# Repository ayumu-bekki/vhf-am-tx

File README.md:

# vhf-am-tx

Seeed Studio XIAO ESP32C6 を用いた 144MHz帯 終段ドレイン変調 AM(A1A / A2A / A3E)送信機プロジェクト。
ARDF(アマチュア無線方向探知)用のフォックスハンティング送信機(A2A)、手動キーのCW送信機(A1A)、および音声AM送信機(A3E)として動作します。

## 主な仕様

- **送信周波数**: 144.000 〜 146.000 MHz(20 kHz ステップ、Si5351A PLL制御)
- **電波型式**:
  - **A1A**: 搬送波断続の電信(CWモード専用)
  - **A2A**: トーン変調電信(700 Hz 正弦波、ARDF 5分サイクル・MOE/MOI/MOS/MOH/MO5・MO/S連続送信対応)
  - **A3E**: 振幅変調電話(マイク入力・デジタル音声信号処理 300 Hz〜3 kHz)
- **送信出力**: 搬送波 1.5 W / 変調ピーク 6.0 W(終段 LDMOS `HTL7G06S006P`)。1.5 W / 500 mW / 100 mW の3段から選択可能
- **変調方式**: 終段ドレイン変調(高レベル変調：250 kHz PWM + 2段RCフィルタ + `TLV9301` / `DMN6068LK3-13` シリーズパスレギュレータ)
- **電源電圧**: DC 12.8 V(4S LiFePO4 バッテリー、10.5〜17 V 対応、低電圧警告・送信禁止保護機能付き)
- **ユーザーインターフェース**: I2C キャラクタ LCD(`AQM1602Y` / ST7032)+ 3ボタン操作(Mode / Fn+ / Fn-)

## 動作モード

`Mode` ボタンで次の順に切り替わります(Fn+ = SW1、Fn- = SW2)。

| モード | 内容 |
|---|---|
| VOICE | A3E 音声。Fn+ を押している間だけ送信 |
| CW | A1A 手動キー。Fn+ を押している間だけ送信 |
| ARDF | A2A 自動送信。Fn+ で開始、**Fn+ の1秒長押しで停止** |
| FREQ | 周波数(20 kHz ステップ) |
| PWR | 出力切り替え(H:1.5 W / M:500mW / L:100mW) |
| CALL | コールサイン編集 |
| ID | ARDF 識別信号(MOE / MOI / MOS / MOH / MO5 / MO) |
| WPM | CW 速度(5〜40) |

- LCD 上段の右端に出力の段を `H`(1.5 W)/ `M`(500 mW)/ `L`(100 mW)で、VOICE・CW・ARDF モードのときだけ常時表示します(FAULT 表示中は出しません。PWR モードは上段が `H:1.5W` / `M:500mW` / `L:100mW`)。下段の右端はバッテリー電圧です。
- `idf.py menuconfig` の `AM Transmitter` メニューで **ARDF モード**と **CW モード**を個別に無効にできます。ARDF を無効にすると ARDF・ID・WPM の各モードが巡回から外れます(CALL は残ります)。デバッグ用のテストモード(`D:DUTY` / `D:CARR` / `D:TONE` / `D:DOT` / `D:BRST`)も同じメニューで有効にします。`D:DOT` は A1A の短点を連続送出し、`D:CARR` の S は PWR で選んだ段の搬送波を出します。

## ディレクトリ構成

```text
.
├── app/vhf-am-tx/    # ESP-IDF ファームウェア(ESP32-C6 / C++)
│   ├── main/         # アプリケーション本体ソースコード
│   └── test/         # ホストPC上で実行可能な単体テスト
├── pcb/vhf-am-tx/    # KiCad 基板設計データ(100×100mm 2層基板)およびガーバーデータ
└── docs/             # ハードウェア設計書(回路・定数・部品表・立ち上げ調整記録)
```

## ビルドとテスト

### ファームウェアのビルド・書き込み

本ファームウェアは **ESP-IDF**(ターゲット: `esp32c6`)を使用します。

```sh
cd app/vhf-am-tx
idf.py set-target esp32c6
idf.py build
idf.py flash monitor
```

> **Note**: 実機で USB ケーブルを接続して書き込みを行う際は、基板上のジャンパ `J9`(U6 AP63301 3.3V出力 ↔ XIAO 3V3)を取り外し、電源の競合を避けてください。また、ベンチテスト時やデバッグモードを有効化する場合は `idf.py menuconfig` の `AM Transmitter` メニューから設定を変更できます。

### ホスト単体テストの実行

CWキーヤ(A1A の波形と CLK0 切り替えのタイミングを含む)・ARDFスケジューラ・出力の段のデューティ写像・送信シーケンス(ドレイン電圧ランプダウン後のキャリア遮断順序など)のロジックは、実機なしでホストPC上で高速にテストできます。

```sh
cd app/vhf-am-tx/test
./run_tests.sh
```

## ドキュメント

コイルの巻き方、組み立てと調整の手順、送信機の構成とスプリアス対策については以下を参照してください。

| 資料 | 内容 |
|---|---|
| [実装ガイド](docs/build-guide.md) | 手巻きインダクタ、DMN6068LK3-13 の取り付け、検波プローブ、ブロックごとの組み立てと調整、最終確認表 |
| [送信機系統図及び技術説明書](docs/jard-tx-system.md) | 主要諸元、送信機系統図、各部の構成と動作、電波型式ごとの送出動作、スプリアス規格への適合(JARD 申請添付用) |
| [ホスト単体テスト](app/vhf-am-tx/test/README.md) | |

| 項目 | 値 |
|---|---|
| 周波数 | 144 MHz 帯（Si5351A） |
| 電波型式 | A1A / A2A / A3E |
| 最大出力 | 搬送波 1.5 W（ピーク 6 W）|
| 変調 | 終段ドレイン変調（TLV9301 ＋ DMN6068LK3-13 のシリーズパス） |
| 終段 / ドライバ | HTL7G06S006P（C級）/ 2SC3357（A級） |
| MCU | Seeed XIAO ESP32-C6 |
| 電源 | 4S LiFePO4（12.8 V） |

## ライセンス

本プロジェクトは [CERN Open Hardware Licence Version 2 - Permissive (CERN-OHL-P v2)](LICENSE) のもとで公開されています。

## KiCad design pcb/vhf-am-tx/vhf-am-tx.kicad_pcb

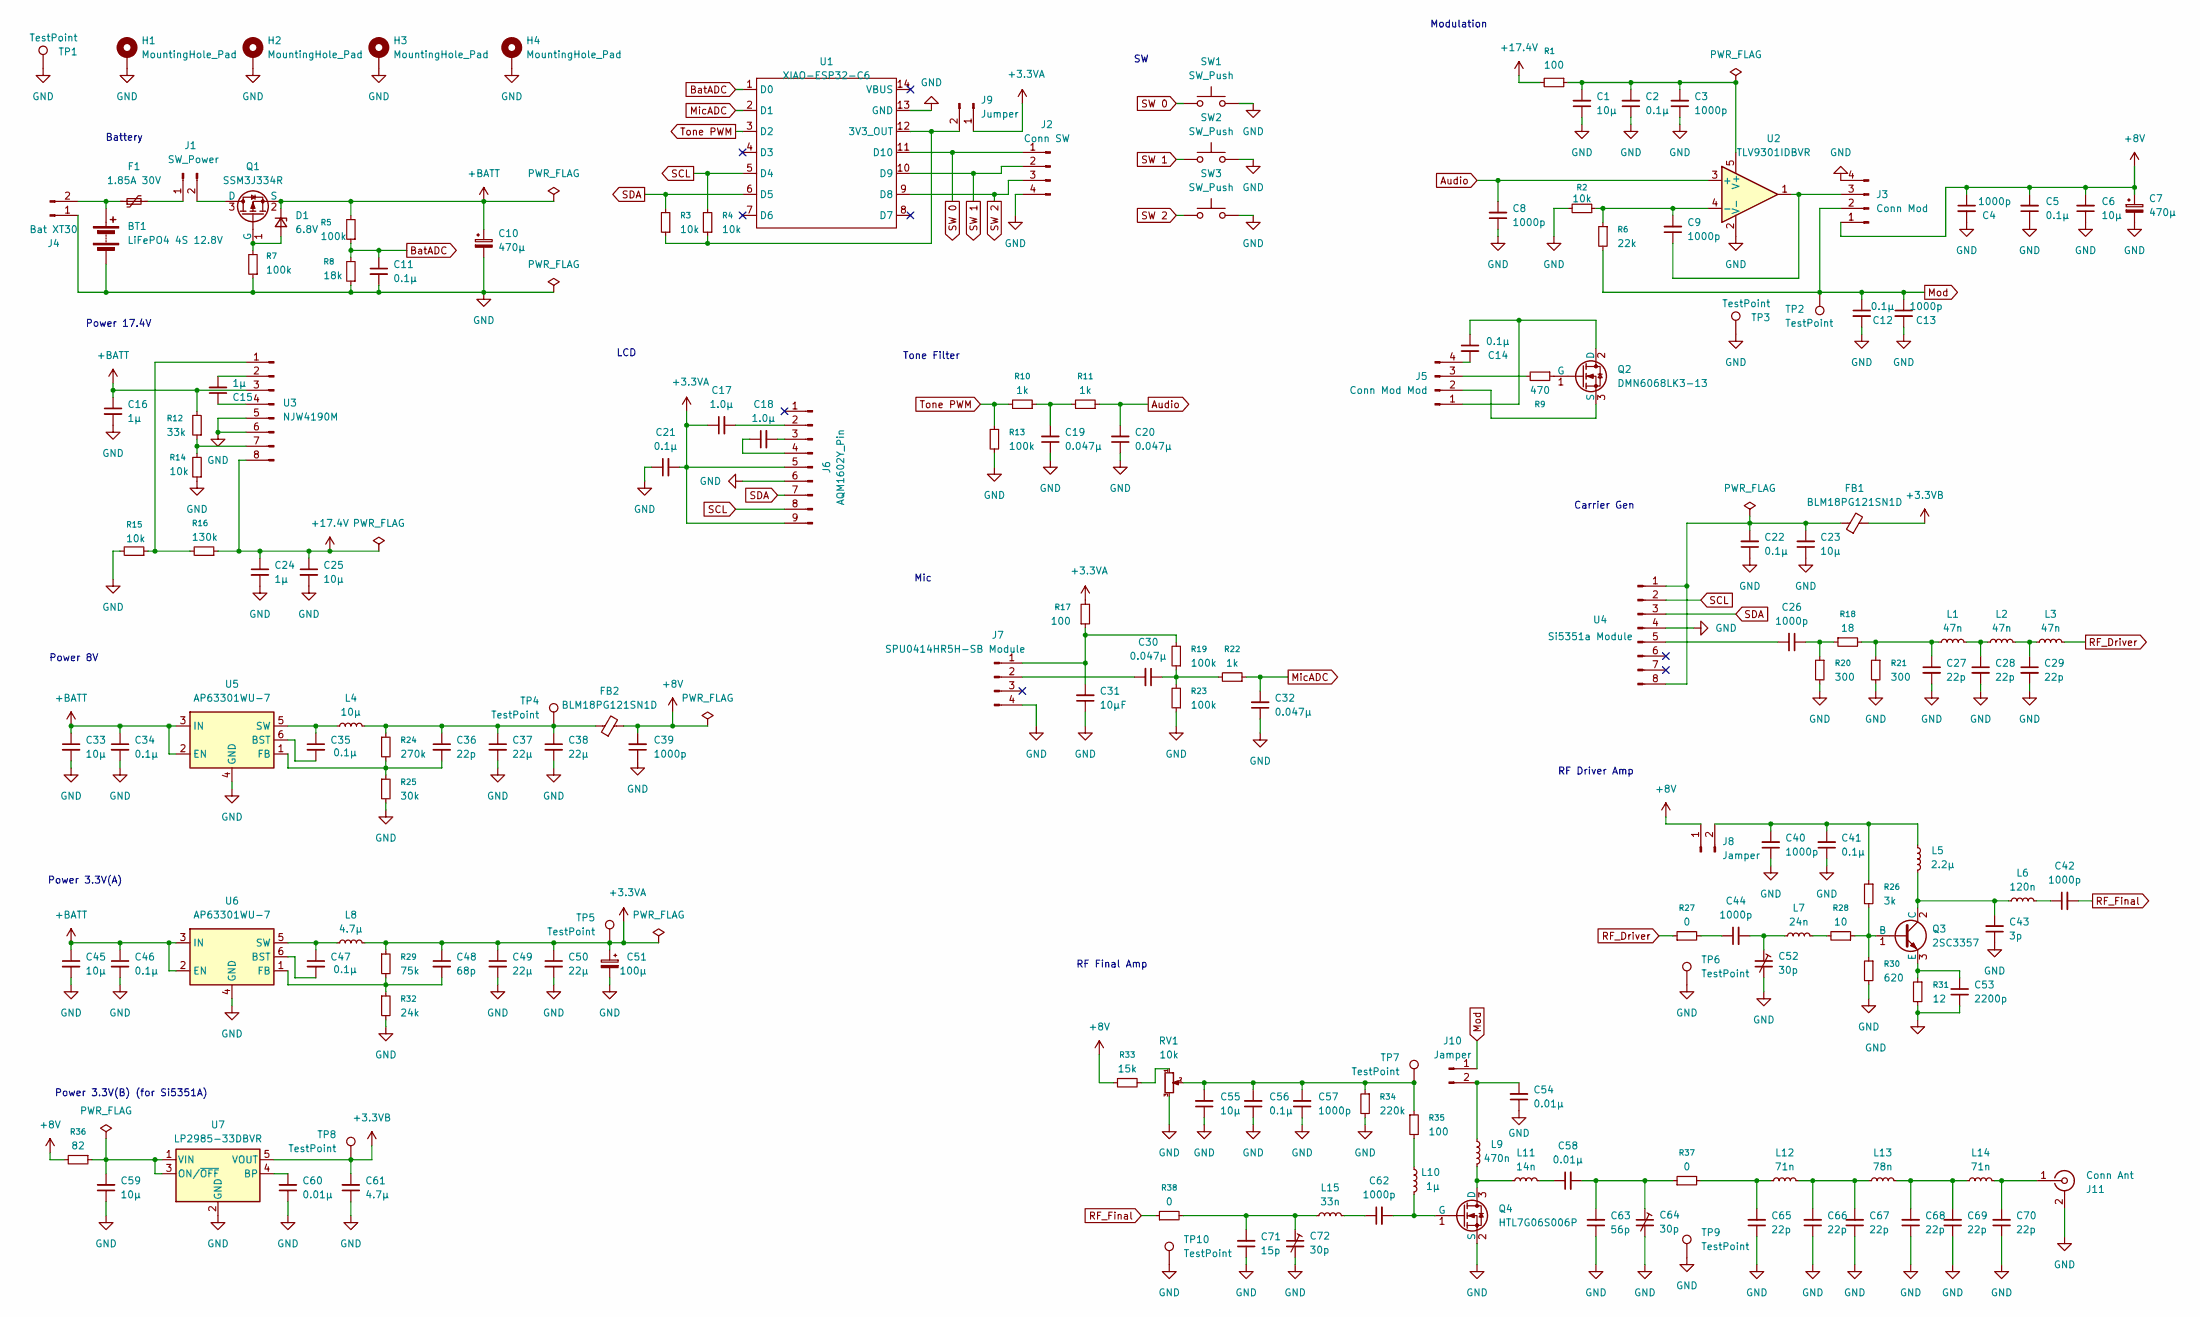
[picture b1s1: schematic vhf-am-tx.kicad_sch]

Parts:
BT1: LiFePO4 4S 12.8V
C1, C6, C23, C25, C33, C45, C55, C59: 10μ; C_0603_1608Metric_Pad1.08x0.95mm_HandSolder
C2, C5, C11, C12, C14, C21, C22, C34, C35, C41, C46, C47, C56: 0.1μ; C_0603_1608Metric_Pad1.08x0.95mm_HandSolder
C3, C4, C8, C9, C13, C26, C39, C40, C42, C44, C57, C62: 1000p; C_0603_1608Metric_Pad1.08x0.95mm_HandSolder
C7, C10: 470μ; CP_Elec_8x10.5
C15, C16, C24: 1μ; C_0603_1608Metric_Pad1.08x0.95mm_HandSolder
C17, C18: 1.0μ; C_0603_1608Metric_Pad1.08x0.95mm_HandSolder
C19, C20, C32: 0.047μ; C_0603_1608Metric_Pad1.08x0.95mm_HandSolder
C27, C28, C29, C36, C65, C66, C67, C68, C69, C70: 22p; C_0603_1608Metric_Pad1.08x0.95mm_HandSolder
C30: 0.047µ; C_0603_1608Metric_Pad1.08x0.95mm_HandSolder
C31: 10μF; C_0603_1608Metric_Pad1.08x0.95mm_HandSolder
C37, C38, C49, C50: 22μ; C_0805_2012Metric_Pad1.18x1.45mm_HandSolder
C43: 3p; C_0603_1608Metric_Pad1.08x0.95mm_HandSolder
C48: 68p; C_0603_1608Metric_Pad1.08x0.95mm_HandSolder
C51: 100μ; CP_Elec_8x10.5
C52, C64, C72: 30p; C_Trimmer_Murata_TZC3
C53: 2200p; C_0603_1608Metric_Pad1.08x0.95mm_HandSolder
C54, C60: 0.01μ; C_0603_1608Metric_Pad1.08x0.95mm_HandSolder
C58: 0.01μ; C_1206_3216Metric_Pad1.33x1.80mm_HandSolder
C61: 4.7µ; C_0603_1608Metric_Pad1.08x0.95mm_HandSolder
C63: 56p; C_0603_1608Metric_Pad1.08x0.95mm_HandSolder
C71: 15p; C_0603_1608Metric_Pad1.08x0.95mm_HandSolder
D1: 6.8V; D_SOD-323_HandSoldering
F1: 1.85A 30V; Fuse_Bourns_MF-RHT650
FB1, FB2: BLM18PG121SN1D; L_0805_2012Metric_Pad1.05x1.20mm_HandSolder
H1, H2, H3, H4: MountingHole_Pad; MountingHole_3.2mm_M3_Pad
J1: SW_Power; JST_XH_B2B-XH-A_1x02_P2.50mm_Vertical
J2: Conn SW; JST_PH_B4B-PH-K_1x04_P2.00mm_Vertical
J3: Conn Mod; PinHeader_1x04_P2.54mm_Vertical
J4: Bat XT30; AMASS_XT30PW-M_1x02_P2.50mm_Horizontal
J5: Conn Mod Mod
J6: AQM1602Y_Pin; PinSocket_1x09_P2.54mm_Vertical
J7: SPU0414HR5H-SB Module; PinHeader_1x04_P2.54mm_Vertical
J8, J10: Jamper; PinHeader_1x02_P2.54mm_Vertical
J9: Jumper; PinHeader_1x02_P2.54mm_Vertical
J11: Conn Ant; Coax_RG174_SolderDirect
L1, L2, L3: 47n; L_0805_2012Metric_Pad1.05x1.20mm_HandSolder
L4: 10μ; L_APV_APH0530
L5: 2.2μ; L_0805_2012Metric_Pad1.05x1.20mm_HandSolder
L6: 120n; Inductor_HandWound_SMD_Core5.0mm_W10.0mm
L7: 24n; Inductor_HandWound_SMD_Core5.0mm_W10.0mm
L8: 4.7μ; L_Taiyo-Yuden_MD-5050
L9: 470n; Inductor_HandWound_SMD_Core5.0mm_W10.5mm
L10: 1μ; L_0805_2012Metric_Pad1.05x1.20mm_HandSolder
L11: 14n; Inductor_HandWound_SMD_Core3.0mm_W4.0mm
L12, L14: 71n; Inductor_HandWound_SMD_Core5.0mm_W5.0mm
L13: 78n; Inductor_HandWound_SMD_Core5.0mm_W5.0mm
L15: 33n; Inductor_HandWound_SMD_Core3.0mm_W5.0mm
Q1: SSM3J334R; SOT-23_Handsoldering
Q2: DMN6068LK3-13; TO-252-2
Q3: 2SC3357; SOT-89-3_Handsoldering
Q4: HTL7G06S006P; SOT-89-3_Handsoldering
R1, R17, R35: 100; R_0603_1608Metric_Pad0.98x0.95mm_HandSolder
R2, R3, R4, R14, R15: 10k; R_0603_1608Metric_Pad0.98x0.95mm_HandSolder
R5, R7, R13, R19, R23: 100k; R_0603_1608Metric_Pad0.98x0.95mm_HandSolder
R6: 22k; R_0603_1608Metric_Pad0.98x0.95mm_HandSolder
R8: 18k; R_0603_1608Metric_Pad0.98x0.95mm_HandSolder
R9: 470; R_0603_1608Metric_Pad0.98x0.95mm_HandSolder
R10, R11, R22: 1k; R_0603_1608Metric_Pad0.98x0.95mm_HandSolder
R12: 33k; R_0603_1608Metric_Pad0.98x0.95mm_HandSolder
R16: 130k; R_0603_1608Metric_Pad0.98x0.95mm_HandSolder
R18: 18; R_0603_1608Metric_Pad0.98x0.95mm_HandSolder
R20, R21: 300; R_0603_1608Metric_Pad0.98x0.95mm_HandSolder
R24: 270k; R_0603_1608Metric_Pad0.98x0.95mm_HandSolder
R25: 30k; R_0603_1608Metric_Pad0.98x0.95mm_HandSolder
R26: 3k; R_0603_1608Metric_Pad0.98x0.95mm_HandSolder
R27, R37, R38: 0; R_2512_6332Metric_Pad1.40x3.35mm_HandSolder
R28: 10; R_0603_1608Metric_Pad0.98x0.95mm_HandSolder
R29: 75k; R_0603_1608Metric_Pad0.98x0.95mm_HandSolder
R30: 620; R_0603_1608Metric_Pad0.98x0.95mm_HandSolder
R31: 12; R_0603_1608Metric_Pad0.98x0.95mm_HandSolder
R32: 24k; R_0603_1608Metric_Pad0.98x0.95mm_HandSolder
R33: 15k; R_0603_1608Metric_Pad0.98x0.95mm_HandSolder
R34: 220k; R_0603_1608Metric_Pad0.98x0.95mm_HandSolder
R36: 82; R_0603_1608Metric_Pad0.98x0.95mm_HandSolder
RV1: 10k; TSR-3296W
SW1, SW2, SW3: SW_Push
TP1: TestPoint; TestPoint_THTPad_D2.0mm_Drill1.0mm
TP2, TP3, TP4, TP5, TP6, TP7, TP8, TP9, TP10: TestPoint; TestPoint_Pad_2.0x2.0mm
U1: XIAO-ESP32-C6; XIAO-ESP32-C6-DIP
U2: TLV9301IDBVR; SOT-23-5
U3: NJW4190M; SOIC-8_5.3x5.3mm_P1.27mm
U4: Si5351a Module; DIP-8_W7.62mm
U5, U6: AP63301WU-7; TSOT-23-6
U7: LP2985-33DBVR; SOT-23-5

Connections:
+3.3VA: C17.1, C21.2, C48.1, C49.1, C50.1, C51.1, J6.5, J6.9, J9.1, L8.2, R17.2, R29.1, TP5.1 (1_1)
+3.3VB: C61.2, FB1.2, TP8.1 (1_1), U7.5 (VOUT)
+8V: C4.1, C5.2, C6.2, C7.1, C39.2, FB2.2, J3.1, J8.1, R33.1, R36.2
+17.4V: C24.1, C25.1, R1.2, R16.1, U3.8
+BATT: C10.1, C16.1, C33.1, C34.1, C45.1, C46.1, D1.1 (K), Q1.2 (S), R5.2, R12.2, U3.3, U5.2 (EN), U5.3 (IN), U6.2 (EN), U6.3 (IN)
Audio: C8.2, C20.2, R11.1, U2.3 (+)
BatADC: C11.1, R5.1, R8.2, U1.1 (D0)
GND: BT1.2 (-), C1.1, C2.1, C3.1, C4.2, C5.1, C6.1, C7.2, C8.1, C10.2, C11.2, C12.2, C13.2, C16.2, C19.1, C20.1, C21.1, C22.1, C23.1, C24.2, C25.2, C27.2, C28.2, C29.2, C31.1, C32.1, C33.2, C34.2, C37.2, C38.2, C39.1, C40.1, C41.1, C43.1, C45.2, C46.2, C49.2, C50.2, C51.2, C52.2, C53.1, C54.1, C55.1, C56.1, C57.1, C59.1, C60.1, C61.1, C63.1, C64.2, C65.1, C66.1, C67.1, C68.1, C69.1, C70.1, C71.1, C72.2, H1.1 (1_1), H2.1 (1_1), H3.1 (1_1), H4.1 (1_1), J2.4, J3.4, J4.1, J6.6, J7.4, J11.2 (Ext), Q4.2 (S), R2.2, R7.1, R8.1, R13.2, R14.1, R15.2, R20.2, R21.2, R23.1, R25.2, R30.2, R31.2, R32.2, R34.2, RV1.3, SW1.2, SW2.2, SW3.2, TP1.1 (1_1), TP3.1 (1_1), TP6.1 (1_1), TP9.1 (1_1), TP10.1 (1_1), U1.13 (GND), U2.2 (V-), U3.5, U3.6, U4.4, U5.4 (GND), U6.4 (GND), U7.2 (GND)
MicADC: C32.2, R22.1, U1.2 (D1)
Mod: C12.1, C13.1, J3.2, J10.1, R6.2, TP2.1 (1_1)
unnamed: C14.1, J5.1, Q2.2 (D)
unnamed: C14.2, J5.4
unnamed: C19.2, R10.1, R11.2
unnamed: C26.1, R18.1, R20.1
unnamed: C27.1, L1.1, R18.2, R21.1
unnamed: C28.1, L1.2, L2.1
unnamed: C29.1, L2.2, L3.1
unnamed: C30.1, R19.1, R22.2, R23.2
unnamed: C36.1, C37.1, C38.1, FB2.1, L4.2, R24.1, TP4.1 (1_1)
unnamed: C42.1, L6.2
unnamed: C44.1, R27.2
unnamed: C44.2, C52.1, L7.1
unnamed: C55.2, C56.2, C57.2, R34.1, R35.1, RV1.2, TP7.1 (1_1)
unnamed: C58.1, L11.2
unnamed: C58.2, C63.2, C64.1, R37.1
unnamed: C62.1, L15.2
unnamed: C65.2, L12.1, R37.2
unnamed: C66.2, C67.2, L12.2, L13.1
unnamed: C68.2, C69.2, L13.2, L14.1
unnamed: C71.2, C72.1, L15.1, R38.2
unnamed: D1.2 (A), Q1.1 (G), R7.2
unnamed: F1.2, J1.1
unnamed: J1.2, Q1.3 (D)
unnamed: C9.1, J3.3, U2.1
unnamed: BT1.1 (+), F1.1, J4.2
unnamed: J5.2, Q2.3 (S)
unnamed: J5.3, R9.2
unnamed: C17.2, J6.2
unnamed: C18.2, J6.3
unnamed: C18.1, J6.4
unnamed: C31.2, J7.1, R17.1, R19.2
unnamed: C30.2, J7.2
unnamed: C40.2, C41.2, J8.2, L5.2, R26.1
unnamed: J9.2, R3.1, R4.1, U1.12 (3V3_OUT)
unnamed: C54.2, J10.2, L9.2
unnamed: C70.2, J11.1 (In), L14.2
unnamed: L7.2, R28.2
unnamed: L10.2, R35.2
unnamed: Q2.1 (G), R9.1
unnamed: Q3.1 (B), R26.2, R28.1, R30.1
unnamed: C43.2, L5.1, L6.1, Q3.2 (C)
unnamed: C53.2, Q3.3 (E), R31.1
unnamed: L9.1, L11.1, Q4.3 (D)
unnamed: C62.2, L10.1, Q4.1 (G)
unnamed: R33.2, RV1.1
unnamed: C9.2, R2.1, R6.1, U2.4 (-)
unnamed: C1.2, C2.2, C3.2, R1.1, U2.5 (V+)
unnamed: R15.1, R16.2, U3.1
unnamed: C15.2, U3.2
unnamed: C15.1, U3.4
unnamed: R12.1, R14.2, U3.7
unnamed: C22.2, C23.2, FB1.1, U4.1, U4.8
unnamed: C26.2, U4.5
unnamed: C35.2, U5.6 (BST)
unnamed: C36.2, R24.2, R25.1, U5.1 (FB)
unnamed: C35.1, L4.1, U5.5 (SW)
unnamed: C47.2, U6.6 (BST)
unnamed: C48.2, R29.2, R32.1, U6.1 (FB)
unnamed: C47.1, L8.1, U6.5 (SW)
unnamed: C60.2, U7.4 (BP)
unnamed: C59.2, R36.1, U7.1 (VIN), U7.3 (ON/~OFF)
RF_Driver: L3.2, R27.1
RF_Final: C42.2, R38.1
SCL: J6.8, R4.2, U1.5 (D4), U4.2
SDA: J6.7, R3.2, U1.6 (D5), U4.3
SW 0: J2.1, SW1.1, U1.11 (D10)
SW 1: J2.2, SW2.1, U1.10 (D9)
SW 2: J2.3, SW3.1, U1.9 (D8)
Tone PWM: R10.2, R13.1, U1.3 (D2)

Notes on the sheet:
Battery
RF Driver Amp
Carrier Gen
Modulation
LCD
Power 17.4V
Mic
Power 3.3V(B) (for Si5351A)
Power 8V
RF Final Amp
Power 3.3V(A)
Tone Filter

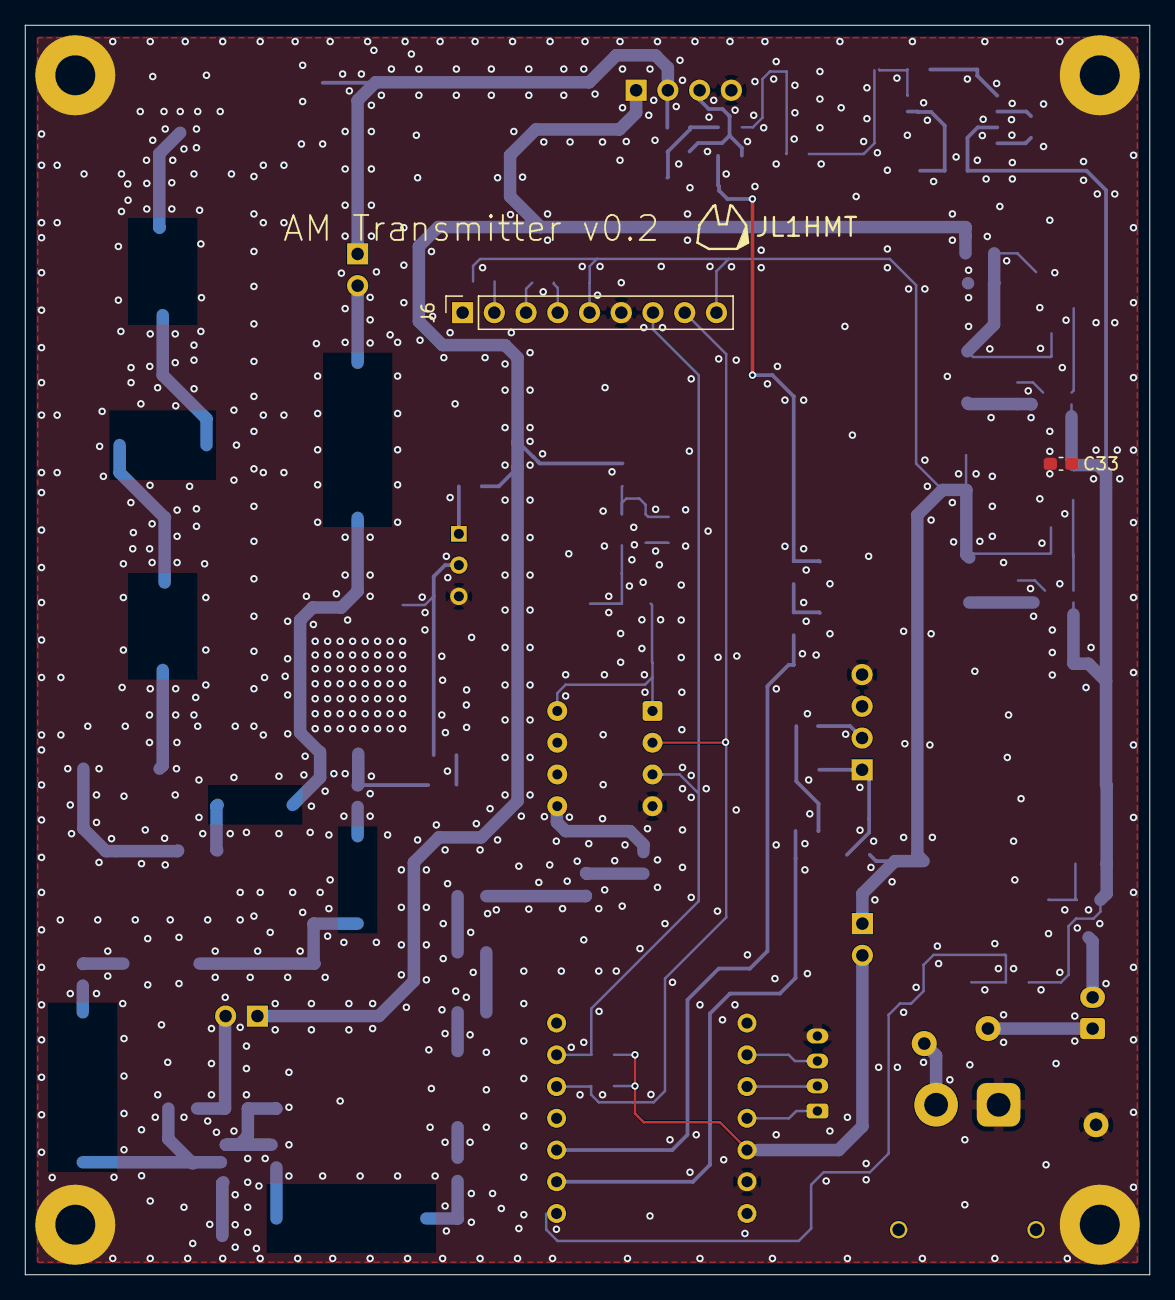
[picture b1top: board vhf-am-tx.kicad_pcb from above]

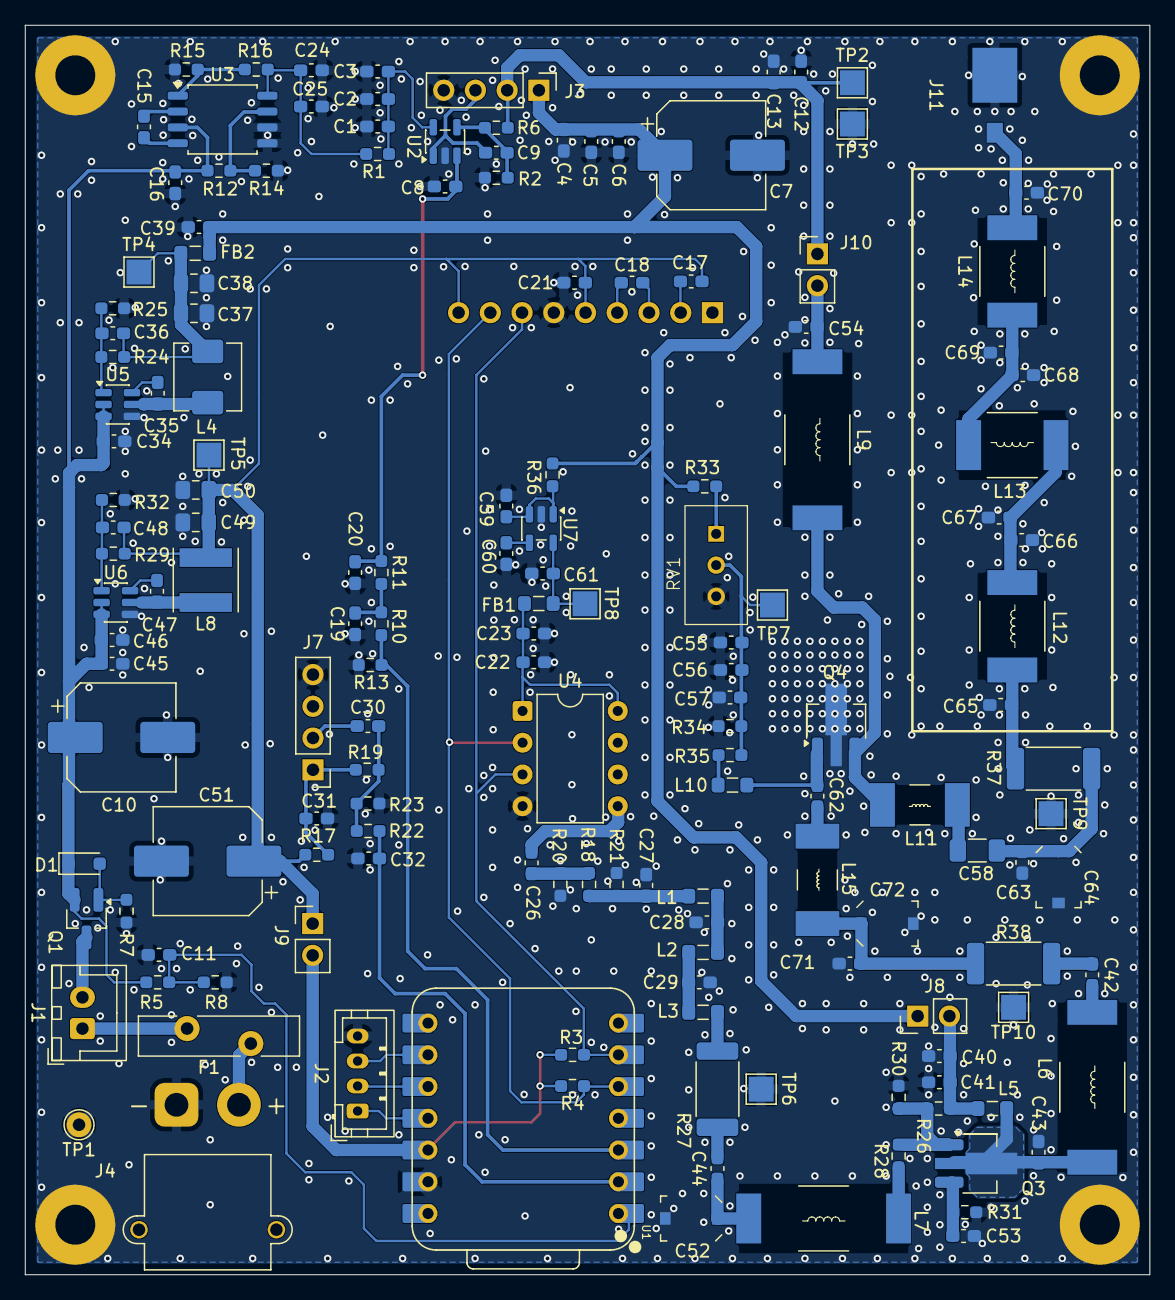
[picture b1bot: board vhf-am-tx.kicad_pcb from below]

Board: 2 copper layers, 90.0 x 100.0 mm, 162 parts (156 on the bottom side), 74 nets.

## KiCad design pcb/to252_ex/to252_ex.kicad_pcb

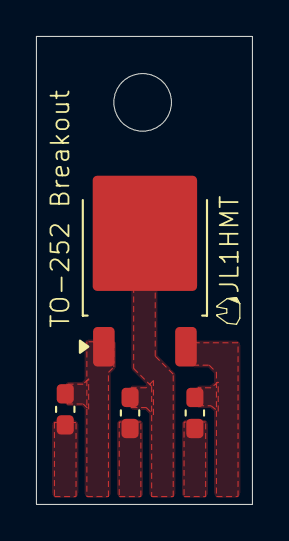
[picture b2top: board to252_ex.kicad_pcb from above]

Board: 2 copper layers, 12.0 x 26.0 mm, 5 parts (0 on the bottom side), 3 nets, no tracks yet.

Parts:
H1: MountingHole; MountingHole_3.2mm_M3
R1, R2, R3: R_Small; C_0603_1608Metric_Pad1.08x0.95mm_HandSolder
U1: TO-252; TO-252-2

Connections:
unnamed: R1.2, U1.1
unnamed: R2.2, U1.2
unnamed: R3.2, U1.3
